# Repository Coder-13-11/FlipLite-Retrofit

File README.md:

# FlipLite Retrofit

A small attachment that flips a bathroom fan switch and turns it off on a timer. The plug-in tube light will use an Amazon smart plug through Alexa.

Start with one fan attachment and one smart plug. The fan arm should park clear so the switch still works by hand. The adjustable fan timer starts at 12 minutes and runs locally. Check that the tube light comes back on when power returns before relying on its smart plug.

## Files

| Folder or file | Contents |
|---|---|
| [CAD](design/cad) | Editable Python parameters, STEP solids and STL print candidates |
| [Electronics](design/electronics) | Editable EAGLE schematic, unrouted board and component list |
| [KiCad board](design/A1/electronics/node.kicad_pcb) | Imported placement draft |
| [Control code](design/firmware) | Python behavior reference and tests |
| [Firmware draft](design/A1/firmware) | Incomplete ESP32 scaffolding |
| [Current plan](design/design-basis.md) | Fan servo plus tube smart plug |
| [Build list](design/active-build-list.md) | Current quantities and print scope |
| [BOM](bom.csv) | Parts categories and links; incomplete pricing |
| [Build guide](design/assembly-and-test.md) | Fit checks and bench tests still needed |
| [Status](STATUS.md) | What exists and what is missing |

## Status

The design is unfinished. The PCB needs routing, verified footprints and electrical checks. The battery is not selected. Firmware and a complete assembly with electronics still need work. No physical prototype has been built or tested.

Inline cradle/finger/optical files are from an earlier approach and are not part of the current build. See [retired files](design/cad/RETIRED.md). Images are CAD or placement renders, not photographs or screenshots of a finished device.

## Checks

Earlier A0 reports recorded 21 passing checks. The upload rerun passed 20; one geometry test could not import OCP.OCP. These tests cover selected geometry/interfaces and control rules, not physical or electrical performance.

```sh
python -m pip install cadquery==2.8.0 trimesh matplotlib pytest
python -m pytest design/validation/test_artifacts.py design/firmware/test_control.py -q
```

## Assistance

AI helped create the CAD, circuit drafts, code and documentation. The files need the builder's own review and revisions. This repository does not establish eligibility for a funding program.

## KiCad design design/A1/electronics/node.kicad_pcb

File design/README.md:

# Design files

Start with the [repository README](../README.md) and [current plan](design-basis.md).

The current build uses a servo for the bathroom fan and a smart plug for the tube light. Older inline actuator parts are retained as history and should not be printed for this build.

[Status and missing requirements](../STATUS.md) lists what still needs to be finished. [View notes](previews/README.md) explains the simplified renders.

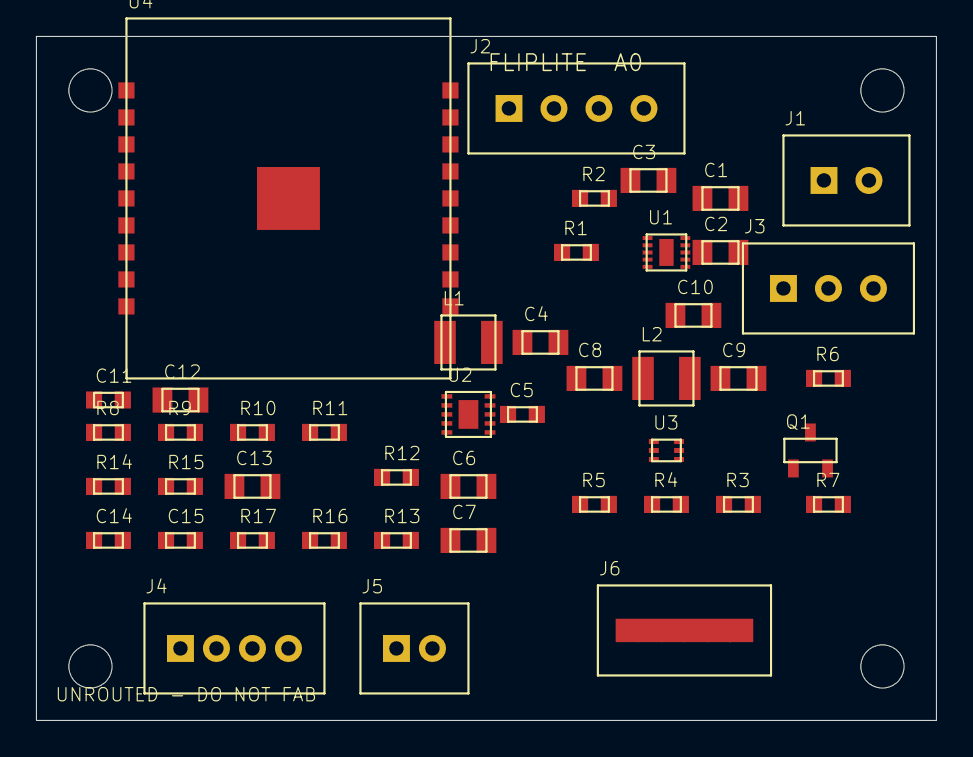
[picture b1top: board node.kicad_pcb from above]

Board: 2 copper layers, 50.0 x 38.0 mm, 49 parts (0 on the bottom side), 29 nets, no tracks yet.

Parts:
C1: 1uF 16V; C1_PKG
C2: 10uF 10V; C2_PKG
C3: 1uF 10V; C3_PKG
C4: 10uF 10V; C4_PKG
C5: 100nF; C5_PKG
C6: 10uF 10V; C6_PKG
C7: 10uF 10V; C7_PKG
C8: 10uF 10V; C8_PKG
C9: 22uF 10V; C9_PKG
C10: 22uF 10V; C10_PKG
C11: 100nF; C11_PKG
C12: 10uF 10V; C12_PKG
C13: 1uF; C13_PKG
C14: 100nF; C14_PKG
C15: 100nF; C15_PKG
J1: B2B-XH-A input; J1_PKG
J2: B4B-XH-A battery+NTC; J2_PKG
J3: B3B-XH-A servo harness; J3_PKG
J4: B4B-PH-K-S dual Hall; J4_PKG
J5: B2B-PH-K-S optical; J5_PKG
J6: Factory pogo fixture; J6_PKG
L1: 1.5uH Isat>=1.5A; L1_PKG
L2: 1uH Isat>=5A; L2_PKG
Q1: 2N7002; Q1_PKG
R1: 18k 1%; R1_PKG
R2: 3.00k 1%; R2_PKG
R3: 732k 1%; R3_PKG
R4: 100k 1%; R4_PKG
R5: 100k; R5_PKG
R6: 4.7k; R6_PKG
R7: 100k; R7_PKG
R8: 10k; R8_PKG
R9: 10k; R9_PKG
R10: 10k; R10_PKG
R11: 10k; R11_PKG
R12: 10k; R12_PKG
R13: 10k; R13_PKG
R14: 470k 1%; R14_PKG
R15: 470k 1%; R15_PKG
R16: 22k; R16_PKG
R17: 1k; R17_PKG
U1: BQ25185DLHR; U1_PKG
U2: TPS63031DSKR; U2_PKG
U3: TPS61023DRLR; U3_PKG
U4: ESP32-C3-WROOM-02-N4; U4_PKG
UNK_HOLE_0: dummyfp0
UNK_HOLE_1: dummyfp1
UNK_HOLE_2: dummyfp2
UNK_HOLE_3: dummyfp3

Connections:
3V3: C6.1, C7.1, C11.1, C12.1, J4.1, J5.1, J6.2, R8.1, R9.1, R10.1, R11.1, R12.1, R13.1, U2.1, U2.10, U4.1
BAT: C3.1, J2.1, R14.1, U1.2
BAT_ADC: C14.1, R14.2, R15.1, U4.15
BOOST_FB: R3.2, R4.1, U3.1
BOOST_SW: L2.2, U3.5
BOOT2: R9.2, U4.16
BOOT8: R10.2, U4.7
BOOT9: J6.5, R11.2, U4.8
CHG_STAT1: R12.2, U1.9, U4.10
CHG_STAT2: R13.2, U1.3, U4.18
GND: C1.2, C2.2, C3.2, C4.2, C5.2, C6.2, C7.2, C8.2, C9.2, C10.2, C11.2, C12.2, C13.2, C14.2, C15.2, J1.2, J2.4, J3.1, J4.2, J6.1, Q1.2, R1.2, R2.2, R4.2, R5.2, R7.2, R15.2, R16.2, U1.4, U1.5, U1.11, U2.3, U2.7, U2.9, U2.11, U3.4, U4.9, U4.19
HALL_OFF: J4.3, U4.5
HALL_ON: J4.4, U4.6
ISET: R2.1, U1.8
L1_BB: L1.1, U2.4
L2_BB: L1.2, U2.2
MOTOR5: C9.1, C10.1, J3.2, R3.1, R6.1, U3.6
MOTOR_EN: R5.1, U3.2, U4.4
NTC: J2.2, U1.6
OPT_ADC: C15.1, R17.2, U4.17
OPT_RAW: J5.2, R16.1, R17.1
PWM_INVERTED: Q1.1, R7.1, U4.3
RESET_N: C13.1, J6.6, R8.2, U4.2
SERVO_PWM: J3.3, Q1.3, R6.2
SYS: C2.1, C4.1, C5.1, C8.1, L2.1, U1.1, U2.5, U2.6, U2.8, U3.3
UART_RX: J6.4, U4.11
UART_TX: J6.3, U4.12
VIN5: C1.1, J1.1, U1.10
VSET: R1.1, U1.7
